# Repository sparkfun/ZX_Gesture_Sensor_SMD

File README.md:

SparkFun ZX Distance and Gesture Sensor
========================================

[*ZX Gesture Sensor (13162)*](https://www.sparkfun.com/products/13162)

The ZX Sensor works by bouncing infrared (IR) beams of light from the two LEDs on either side 
off of an object above the sensor. The bounced light returns to the receiver in the center of
the sensor, and a microcontroller on the back of the sensor interprets the data. We can read 
the results using an I2C or UART connection.

Repository Contents
-------------------

* **/Hardware** - Eagle design files (.brd, .sch)
* **/Libraries** - Arduino library and example code. For the most recent updates, make sure to check out the GitHub repo for the Arduino library linked below.
* **/Production** - Production panel files (.brd)

Documentation
--------------
* **[Library](https://github.com/sparkfun/SparkFun_ZX_Distance_and_Gesture_Sensor_Arduino_Library)** - Arduino library for the ZX Distance and Gesture Sensor.
* **[Hookup Guide](https://learn.sparkfun.com/tutorials/zx-distance-and-gesture-sensor-smd-hookup-guide)** - Basic hookup guide for the ZX Gesture Sensor.

License Information
-------------------

This product is _**open source**_! 

Please review the LICENSE.md file for license information. 

If you have any questions or concerns on licensing, please contact techsupport@sparkfun.com.

Distributed as-is; no warranty is given.

- Your friends at SparkFun.

__In Collaboration in XYZ Interactive__

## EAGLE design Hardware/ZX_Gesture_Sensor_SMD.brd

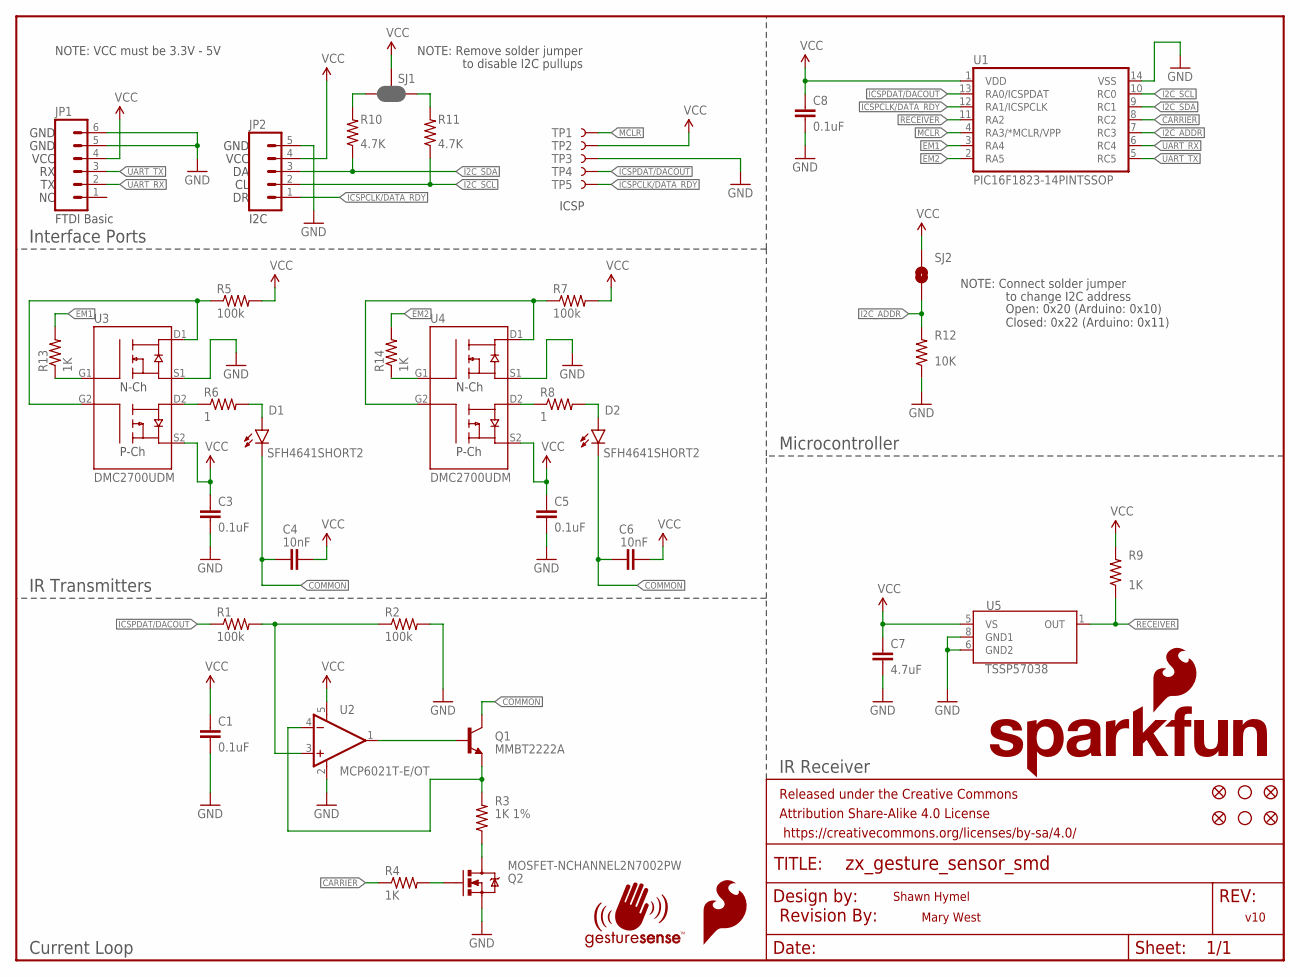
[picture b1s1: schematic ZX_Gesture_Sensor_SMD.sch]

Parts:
C1, C3, C5, C8: 0.1uF; 0603-CAP
C4, C6: 10nF; 0603-CAP
C7: 4.7uF; 0603-CAP
D1, D2: SFH4641SHORT2; SFH4641-SHORT2
FID1, FID2, FID3, FID4: FIDUCIALUFIDUCIAL; MICRO-FIDUCIAL
FRAME1: FRAME-LETTER; CREATIVE_COMMONS
JP1: M06NO_SILK_FEMALE_PTH; 1X06_NO_SILK
JP2: M05PTH; 1X05
LOGO1: REVISION
LOGO2: SFE_LOGO_FLAME.1_INCH; SFE_LOGO_FLAME_.1
Q1: MMBT2222A; SOT23-3
Q2: MOSFET-NCHANNEL2N7002PW; SOT323
R1, R2, R5, R7: 100k; 0603-RES
R3: 1K 1%; 0603-RES
R4, R9, R13, R14: 1K; 0603-RES
R6, R8: 1; 0603-RES
R10, R11: 4.7K; 0603-RES
R12: 10K; 0603-RES
SJ1: JUMPER-PAD-3-NC_BY_PASTE; PAD-JUMPER-3-NC_BY_PASTE_YES_SILK_FULL_BOX
SJ2: JUMPER-PAD-2-NOYES_SILK; PAD-JUMPER-2-NO_YES_SILK
STANDOFF1, STANDOFF2: STAND-OFF
TP1, TP2, TP3, TP4, TP5: TEST-POINT3X4; PAD.03X.04
U1: PIC16F1823-14PINTSSOP; TSSOP14
U2: MCP6021T-E/OT; SOT23-5
U3, U4: DMC2700UDM; SOT26
U5: TSSP57038; TSOP572
U$5: SFE_LOGO_NAME_FLAME.1_INCH; SFE_LOGO_NAME_FLAME_.1
U$6: GESTURESENSE_LOGOSTEXT; GESTURESENSE_TEXT

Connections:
CARRIER: R4.1, U1.8 (RC2)
COMMON: C4.1, C6.1, D1.C, D2.C, Q1.3 (C)
EM1: R13.2, U1.3 (RA4)
EM2: R14.2, U1.2 (RA5)
GND: C1.2, C3.2, C5.2, C7.2, C8.2, JP1.5, JP1.6, JP2.5, Q2.2 (S), R2.2, R12.1, TP3.P$1, U1.14 (VSS), U2.2 (V-), U3.S1, U4.S1, U5.6 (GND2), U5.8 (GND1)
I2C_ADDR: R12.2, SJ2.1, U1.7 (RC3)
I2C_SCL: JP2.2, R11.1, U1.10 (RC0)
I2C_SDA: JP2.3, R10.1, U1.9 (RC1)
ICSPCLK/DATA_RDY: JP2.1, TP5.P$1, U1.12 (RA1/ICSPCLK)
ICSPDAT/DACOUT: R1.1, TP4.P$1, U1.13 (RA0/ICSPDAT)
MCLR: TP1.P$1, U1.4 (RA3/*MCLR/VPP)
unnamed: R1.2, R2.1, U2.3 (+IN)
unnamed: Q1.2 (E), R3.2, U2.4 (-IN)
unnamed: Q1.1 (B), U2.1 (OUT)
unnamed: Q2.3 (D), R3.1
unnamed: Q2.1 (G), R4.2
unnamed: R6.1, U3.D2
unnamed: D1.A, R6.2
unnamed: R5.1, U3.D1, U3.G2
unnamed: R7.1, U4.D1, U4.G2
unnamed: R10.2, SJ1.3
unnamed: R8.1, U4.D2
unnamed: D2.A, R8.2
unnamed: R11.2, SJ1.1
unnamed: R13.1, U3.G1
unnamed: R14.1, U4.G1
RECEIVER: R9.1, U1.11 (RA2), U5.1 (OUT)
UART_RX: JP1.2, U1.6 (RC4)
UART_TX: JP1.3, U1.5 (RC5)
VCC: C1.1, C3.1, C4.2, C5.1, C6.2, C7.1, C8.1, JP1.4, JP2.4, R5.2, R7.2, R9.2, SJ1.2, SJ2.2, TP2.P$1, U1.1 (VDD), U2.5 (V+), U3.S2, U4.S2, U5.5 (VS)

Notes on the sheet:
FTDI Basic
I2C
ICSP
NOTE: Remove solder jumper
to disable I2C pullups
NOTE: Connect solder jumper
to change I2C address
Open: 0x20 (Arduino: 0x10) Closed: 0x22 (Arduino: 0x11)
Interface Ports
IR Transmitters
Current Loop
Microcontroller
IR Receiver
VCC
GND
NOTE: VCC must be 3.3V - 5V
Shawn Hymel
Mary West
v10

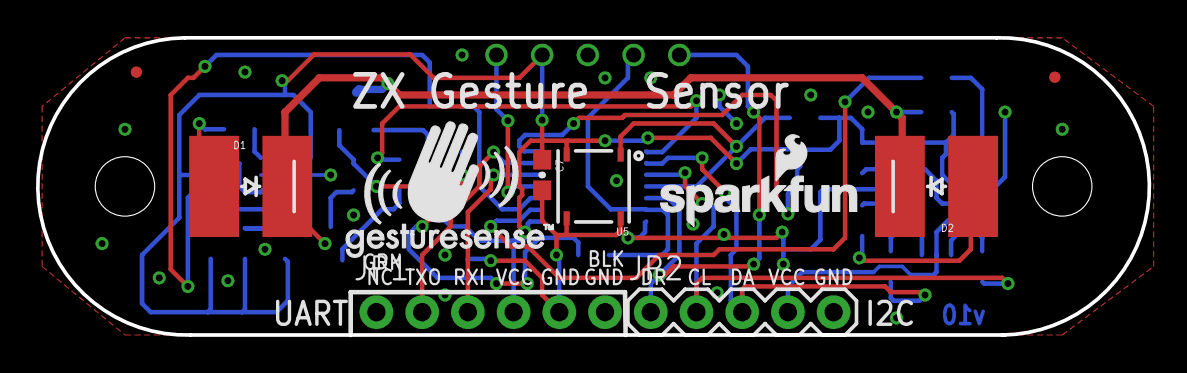
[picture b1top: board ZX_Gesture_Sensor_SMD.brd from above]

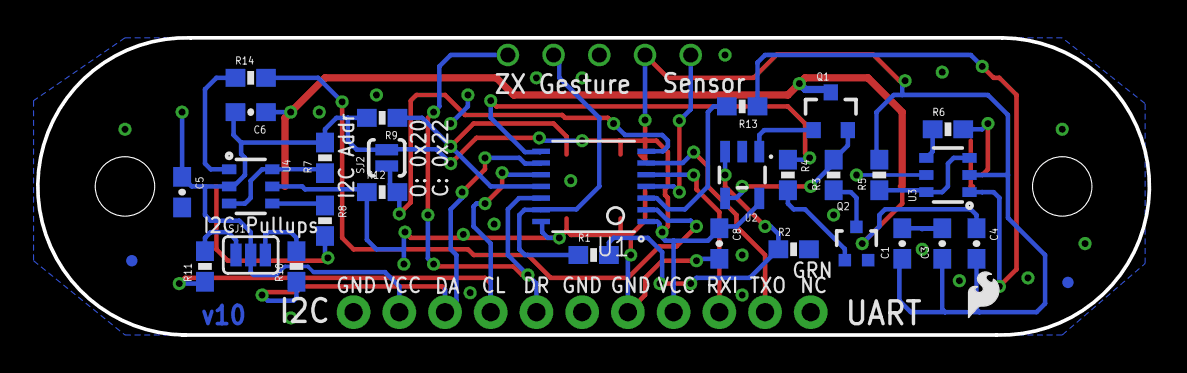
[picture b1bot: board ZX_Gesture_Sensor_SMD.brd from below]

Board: 2 copper layers, 61.8 x 16.5 mm, 50 parts (36 on the bottom side), 30 nets.

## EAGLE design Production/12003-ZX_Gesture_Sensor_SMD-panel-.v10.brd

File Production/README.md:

SparkFun <PRODUCT NAME> Production Files
=========================================

These are the production files SparkFun uses for printing PCBs.

License Information
-------------------
This product is open source! 
The hardware is released under [Creative Commons ShareAlike 4.0 International](https://creativecommons.org/licenses/by-sa/4.0/).
Please use, reuse, and modify these files as you see fit. Please maintain attribution to SparkFun Electronics and release anything derivative under the same license.

Distributed as-is; no warranty is given.

- Your friends at SparkFun.

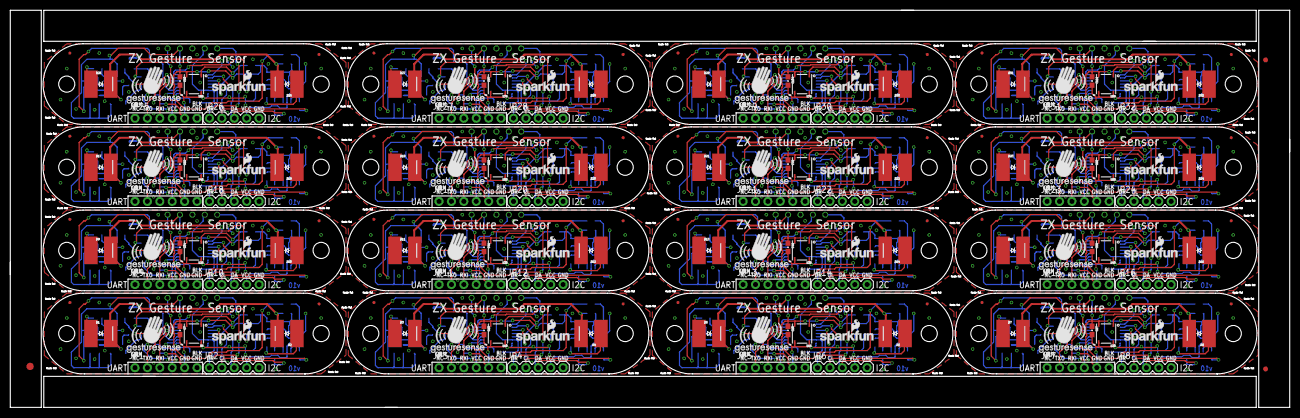
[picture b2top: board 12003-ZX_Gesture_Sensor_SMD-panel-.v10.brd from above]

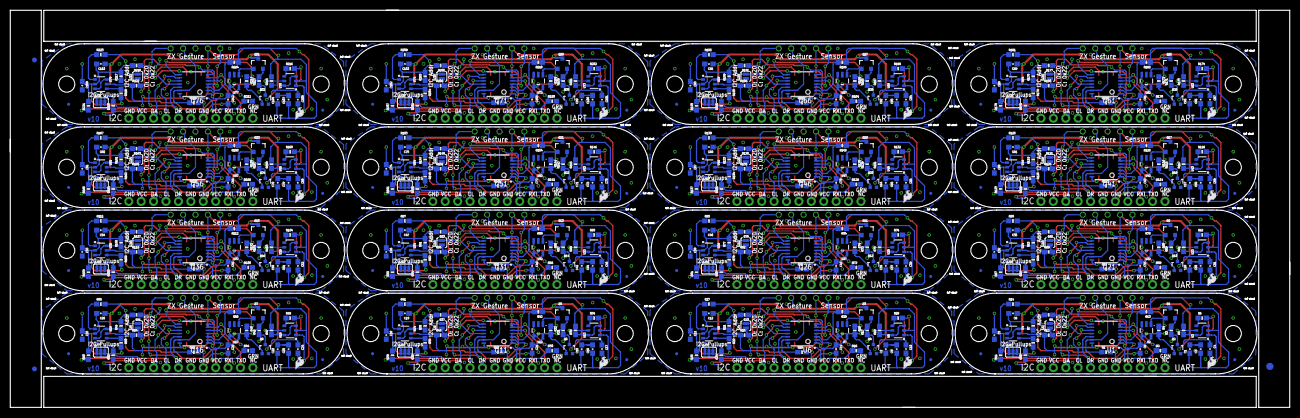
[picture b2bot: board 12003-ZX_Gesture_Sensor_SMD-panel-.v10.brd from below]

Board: 2 copper layers, 261.9 x 81.3 mm, 774 parts (579 on the bottom side), 480 nets.

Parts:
C1, C2, C3, C5, C8, C9, C11, C14, C15, C16, C18, C21, C22, C23, C25, C28, C29, C30, C32, C35, C36, C37, C39, C42, C43, C44, C46, C49, C50, C51, C53, C56, C57, C58, C60, C63, C64, C65, C67, C70, C71, C72, C74, C77, C78, C79, C81, C84, C85, C86, C88, C91, C92, C93, C95, C98, C99, C100, C102, C105, C106, C107, C109, C112: 0.1uF; 0603-CAP
C4, C6, C10, C12, C17, C19, C24, C26, C31, C33, C38, C40, C45, C47, C52, C54, C59, C61, C66, C68, C73, C75, C80, C82, C87, C89, C94, C96, C101, C103, C108, C110: 10nF; 0603-CAP
C7, C13, C20, C27, C34, C41, C48, C55, C62, C69, C76, C83, C90, C97, C104, C111: 4.7uF; 0603-CAP
D1, D2, D3, D4, D5, D6, D7, D8, D9, D10, D11, D12, D13, D14, D15, D16, D17, D18, D19, D20, D21, D22, D23, D24, D25, D26, D27, D28, D29, D30, D31, D32: SFH4641SHORT2; SFH4641-SHORT2
E$1, E$2: FIDUCIAL-1.5X3
E$3, E$4, E$7, E$8: FIDUCIAL-1X2
FID1, FID2, FID3, FID4, FID5, FID6, FID7, FID8, FID9, FID10, FID11, FID12, FID13, FID14, FID15, FID16, FID17, FID18, FID19, FID20, FID21, FID22, FID23, FID24, FID25, FID26, FID27, FID28, FID29, FID30, FID31, FID32, FID33, FID34, FID35, FID36, FID37, FID38, FID39, FID40, FID41, FID42, FID43, FID44, FID45, FID46, FID47, FID48, FID49, FID50, FID51, FID52, FID53, FID54, FID55, FID56, FID57, FID58, FID59, FID60, FID61, FID62, FID63, FID64: FIDUCIALUFIDUCIAL; MICRO-FIDUCIAL
JP1, JP3, JP5, JP7, JP9, JP11, JP13, JP15, JP17, JP19, JP21, JP23, JP25, JP27, JP29, JP31: 1X06_NO_SILK
JP2, JP4, JP6, JP8, JP10, JP12, JP14, JP16, JP18, JP20, JP22, JP24, JP26, JP28, JP30, JP32: 1X05
LOGO1, LOGO2, LOGO3, LOGO4, LOGO5, LOGO6, LOGO7, LOGO8, LOGO9, LOGO10, LOGO11, LOGO12, LOGO13, LOGO14, LOGO15, LOGO16: SFE_LOGO_FLAME.1_INCH; SFE_LOGO_FLAME_.1
Q1, Q3, Q5, Q7, Q9, Q11, Q13, Q15, Q17, Q19, Q21, Q23, Q25, Q27, Q29, Q31: MMBT2222A; SOT23-3
Q2, Q4, Q6, Q8, Q10, Q12, Q14, Q16, Q18, Q20, Q22, Q24, Q26, Q28, Q30, Q32: MOSFET-NCHANNEL2N7002PW; SOT323
R1, R2, R5, R7, R15, R16, R19, R21, R29, R30, R33, R35, R43, R44, R47, R49, R57, R58, R61, R63, R71, R72, R75, R77, R85, R86, R89, R91, R99, R100, R103, R105, R113, R114, R117, R119, R127, R128, R131, R133, R141, R142, R145, R147, R155, R156, R159, R161, R169, R170, R173, R175, R183, R184, R187, R189, R197, R198, R201, R203, R211, R212, R215, R217: 100k; 0603-RES
R3, R17, R31, R45, R59, R73, R87, R101, R115, R129, R143, R157, R171, R185, R199, R213: 1K 1%; 0603-RES
R4, R9, R13, R14, R18, R23, R27, R28, R32, R37, R41, R42, R46, R51, R55, R56, R60, R65, R69, R70, R74, R79, R83, R84, R88, R93, R97, R98, R102, R107, R111, R112, R116, R121, R125, R126, R130, R135, R139, R140, R144, R149, R153, R154, R158, R163, R167, R168, R172, R177, R181, R182, R186, R191, R195, R196, R200, R205, R209, R210, R214, R219, R223, R224: 1K; 0603-RES
R6, R8, R20, R22, R34, R36, R48, R50, R62, R64, R76, R78, R90, R92, R104, R106, R118, R120, R132, R134, R146, R148, R160, R162, R174, R176, R188, R190, R202, R204, R216, R218: 1; 0603-RES
R10, R11, R24, R25, R38, R39, R52, R53, R66, R67, R80, R81, R94, R95, R108, R109, R122, R123, R136, R137, R150, R151, R164, R165, R178, R179, R192, R193, R206, R207, R220, R221: 4.7K; 0603-RES
R12, R26, R40, R54, R68, R82, R96, R110, R124, R138, R152, R166, R180, R194, R208, R222: 10K; 0603-RES
SJ1, SJ3, SJ5, SJ7, SJ9, SJ11, SJ13, SJ15, SJ17, SJ19, SJ21, SJ23, SJ25, SJ27, SJ29, SJ31: JUMPER-PAD-3-NC_BY_PASTE; PAD-JUMPER-3-NC_BY_PASTE_YES_SILK_FULL_BOX
SJ2, SJ4, SJ6, SJ8, SJ10, SJ12, SJ14, SJ16, SJ18, SJ20, SJ22, SJ24, SJ26, SJ28, SJ30, SJ32: JUMPER-PAD-2-NOYES_SILK; PAD-JUMPER-2-NO_YES_SILK
STANDOFF1, STANDOFF2, STANDOFF3, STANDOFF4, STANDOFF5, STANDOFF6, STANDOFF7, STANDOFF8, STANDOFF9, STANDOFF10, STANDOFF11, STANDOFF12, STANDOFF13, STANDOFF14, STANDOFF15, STANDOFF16, STANDOFF17, STANDOFF18, STANDOFF19, STANDOFF20, STANDOFF21, STANDOFF22, STANDOFF23, STANDOFF24, STANDOFF25, STANDOFF26, STANDOFF27, STANDOFF28, STANDOFF29, STANDOFF30, STANDOFF31, STANDOFF32: STAND-OFF
TP1, TP2, TP3, TP4, TP5, TP6, TP7, TP8, TP9, TP10, TP11, TP12, TP13, TP14, TP15, TP16, TP17, TP18, TP19, TP20, TP21, TP22, TP23, TP24, TP25, TP26, TP27, TP28, TP29, TP30, TP31, TP32, TP33, TP34, TP35, TP36, TP37, TP38, TP39, TP40, TP41, TP42, TP43, TP44, TP45, TP46, TP47, TP48, TP49, TP50, TP51, TP52, TP53, TP54, TP55, TP56, TP57, TP58, TP59, TP60, TP61, TP62, TP63, TP64, TP65, TP66, TP67, TP68, TP69, TP70, TP71, TP72, TP73, TP74, TP75, TP76, TP77, TP78, TP79, TP80: TEST-POINT3X4; PAD.03X.04
U1, U6, U11, U16, U21, U26, U31, U36, U41, U46, U51, U56, U61, U66, U71, U76: PIC16F1823-14PINTSSOP; TSSOP14
U2, U7, U12, U17, U22, U27, U32, U37, U42, U47, U52, U57, U62, U67, U72, U77: MCP6021T-E/OT; SOT23-5
U3, U4, U8, U9, U13, U14, U18, U19, U23, U24, U28, U29, U33, U34, U38, U39, U43, U44, U48, U49, U53, U54, U58, U59, U63, U64, U68, U69, U73, U74, U78, U79: DMC2700UDM; SOT26
U5, U10, U15, U20, U25, U30, U35, U40, U45, U50, U55, U60, U65, U70, U75, U80: TSSP57038; TSOP572
U$1, U$3, U$5, U$7, U$9, U$11, U$13, U$15, U$17, U$19, U$21, U$23, U$25, U$27, U$29, U$31: SFE_LOGO_NAME_FLAME.1_INCH; SFE_LOGO_NAME_FLAME_.1
U$2, U$4, U$6, U$8, U$10, U$12, U$14, U$16, U$18, U$20, U$22, U$24, U$26, U$28, U$30, U$32: GESTURESENSE_LOGOSTEXT; GESTURESENSE_TEXT

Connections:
CARRIER: R4.1, U1.8
CARRIER1: R18.1, U6.8
CARRIER2: R32.1, U11.8
CARRIER3: R46.1, U16.8
CARRIER4: R60.1, U21.8
CARRIER5: R74.1, U26.8
CARRIER6: R88.1, U31.8
CARRIER7: R102.1, U36.8
CARRIER8: R116.1, U41.8
CARRIER9: R130.1, U46.8
CARRIER10: R144.1, U51.8
CARRIER11: R158.1, U56.8
CARRIER12: R172.1, U61.8
CARRIER13: R186.1, U66.8
CARRIER14: R200.1, U71.8
CARRIER15: R214.1, U76.8
COMMON: C4.1, C6.1, D1.C, D2.C, Q1.3
COMMON1: C10.1, C12.1, D3.C, D4.C, Q3.3
COMMON2: C17.1, C19.1, D5.C, D6.C, Q5.3
COMMON3: C24.1, C26.1, D7.C, D8.C, Q7.3
COMMON4: C31.1, C33.1, D9.C, D10.C, Q9.3
COMMON5: C38.1, C40.1, D11.C, D12.C, Q11.3
COMMON6: C45.1, C47.1, D13.C, D14.C, Q13.3
COMMON7: C52.1, C54.1, D15.C, D16.C, Q15.3
COMMON8: C59.1, C61.1, D17.C, D18.C, Q17.3
COMMON9: C66.1, C68.1, D19.C, D20.C, Q19.3
COMMON10: C73.1, C75.1, D21.C, D22.C, Q21.3
COMMON11: C80.1, C82.1, D23.C, D24.C, Q23.3
COMMON12: C87.1, C89.1, D25.C, D26.C, Q25.3
COMMON13: C94.1, C96.1, D27.C, D28.C, Q27.3
COMMON14: C101.1, C103.1, D29.C, D30.C, Q29.3
COMMON15: C108.1, C110.1, D31.C, D32.C, Q31.3
EM1: R13.2, U1.3
EM2: R14.2, U1.2
EM3: R28.2, U6.3
EM4: R27.2, U6.2
EM5: R42.2, U11.3
EM6: R41.2, U11.2
EM7: R56.2, U16.3
EM8: R55.2, U16.2
EM9: R70.2, U21.3
EM10: R69.2, U21.2
EM11: R84.2, U26.3
EM12: R83.2, U26.2
EM13: R98.2, U31.3
EM14: R97.2, U31.2
EM15: R112.2, U36.3
EM16: R111.2, U36.2
EM17: R126.2, U41.3
EM18: R125.2, U41.2
EM19: R140.2, U46.3
EM20: R139.2, U46.2
EM21: R154.2, U51.3
EM22: R153.2, U51.2
EM23: R168.2, U56.3
EM24: R167.2, U56.2
EM25: R182.2, U61.3
EM26: R181.2, U61.2
EM27: R196.2, U66.3
EM28: R195.2, U66.2
EM29: R210.2, U71.3
EM30: R209.2, U71.2
EM31: R224.2, U76.3
EM32: R223.2, U76.2
GND: C1.2, C3.2, C5.2, C7.2, C8.2, JP1.5, JP1.6, JP2.5, Q2.2, R2.2, R12.1, TP3.P$1, U1.14, U2.2, U3.S1, U4.S1, U5.6, U5.8
GND1: C2.2, C9.2, C11.2, C13.2, C14.2, JP3.5, JP3.6, JP4.5, Q4.2, R16.2, R26.1, TP7.P$1, U6.14, U7.2, U8.S1, U9.S1, U10.6, U10.8
GND2: C15.2, C16.2, C18.2, C20.2, C21.2, JP5.5, JP5.6, JP6.5, Q6.2, R30.2, R40.1, TP12.P$1, U11.14, U12.2, U13.S1, U14.S1, U15.6, U15.8
GND3: C22.2, C23.2, C25.2, C27.2, C28.2, JP7.5, JP7.6, JP8.5, Q8.2, R44.2, R54.1, TP17.P$1, U16.14, U17.2, U18.S1, U19.S1, U20.6, U20.8
GND4: C29.2, C30.2, C32.2, C34.2, C35.2, JP9.5, JP9.6, JP10.5, Q10.2, R58.2, R68.1, TP22.P$1, U21.14, U22.2, U23.S1, U24.S1, U25.6, U25.8
GND5: C36.2, C37.2, C39.2, C41.2, C42.2, JP11.5, JP11.6, JP12.5, Q12.2, R72.2, R82.1, TP27.P$1, U26.14, U27.2, U28.S1, U29.S1, U30.6, U30.8
GND6: C43.2, C44.2, C46.2, C48.2, C49.2, JP13.5, JP13.6, JP14.5, Q14.2, R86.2, R96.1, TP32.P$1, U31.14, U32.2, U33.S1, U34.S1, U35.6, U35.8
GND7: C50.2, C51.2, C53.2, C55.2, C56.2, JP15.5, JP15.6, JP16.5, Q16.2, R100.2, R110.1, TP37.P$1, U36.14, U37.2, U38.S1, U39.S1, U40.6, U40.8
GND8: C57.2, C58.2, C60.2, C62.2, C63.2, JP17.5, JP17.6, JP18.5, Q18.2, R114.2, R124.1, TP42.P$1, U41.14, U42.2, U43.S1, U44.S1, U45.6, U45.8
GND9: C64.2, C65.2, C67.2, C69.2, C70.2, JP19.5, JP19.6, JP20.5, Q20.2, R128.2, R138.1, TP47.P$1, U46.14, U47.2, U48.S1, U49.S1, U50.6, U50.8
GND10: C71.2, C72.2, C74.2, C76.2, C77.2, JP21.5, JP21.6, JP22.5, Q22.2, R142.2, R152.1, TP52.P$1, U51.14, U52.2, U53.S1, U54.S1, U55.6, U55.8
GND11: C78.2, C79.2, C81.2, C83.2, C84.2, JP23.5, JP23.6, JP24.5, Q24.2, R156.2, R166.1, TP57.P$1, U56.14, U57.2, U58.S1, U59.S1, U60.6, U60.8
GND12: C85.2, C86.2, C88.2, C90.2, C91.2, JP25.5, JP25.6, JP26.5, Q26.2, R170.2, R180.1, TP62.P$1, U61.14, U62.2, U63.S1, U64.S1, U65.6, U65.8
GND13: C92.2, C93.2, C95.2, C97.2, C98.2, JP27.5, JP27.6, JP28.5, Q28.2, R184.2, R194.1, TP67.P$1, U66.14, U67.2, U68.S1, U69.S1, U70.6, U70.8
GND14: C99.2, C100.2, C102.2, C104.2, C105.2, JP29.5, JP29.6, JP30.5, Q30.2, R198.2, R208.1, TP72.P$1, U71.14, U72.2, U73.S1, U74.S1, U75.6, U75.8
GND15: C106.2, C107.2, C109.2, C111.2, C112.2, JP31.5, JP31.6, JP32.5, Q32.2, R212.2, R222.1, TP77.P$1, U76.14, U77.2, U78.S1, U79.S1, U80.6, U80.8
I2C_ADDR: R12.2, SJ2.1, U1.7
I2C_ADDR1: R26.2, SJ4.1, U6.7
I2C_ADDR2: R40.2, SJ6.1, U11.7
I2C_ADDR3: R54.2, SJ8.1, U16.7
I2C_ADDR4: R68.2, SJ10.1, U21.7
I2C_ADDR5: R82.2, SJ12.1, U26.7
I2C_ADDR6: R96.2, SJ14.1, U31.7
I2C_ADDR7: R110.2, SJ16.1, U36.7
I2C_ADDR8: R124.2, SJ18.1, U41.7
I2C_ADDR9: R138.2, SJ20.1, U46.7
I2C_ADDR10: R152.2, SJ22.1, U51.7
I2C_ADDR11: R166.2, SJ24.1, U56.7
I2C_ADDR12: R180.2, SJ26.1, U61.7
I2C_ADDR13: R194.2, SJ28.1, U66.7
I2C_ADDR14: R208.2, SJ30.1, U71.7
I2C_ADDR15: R222.2, SJ32.1, U76.7
I2C_SCL: JP2.2, R11.1, U1.10
I2C_SCL1: JP4.2, R25.1, U6.10
I2C_SCL2: JP6.2, R39.1, U11.10
I2C_SCL3: JP8.2, R53.1, U16.10
I2C_SCL4: JP10.2, R67.1, U21.10
I2C_SCL5: JP12.2, R81.1, U26.10
I2C_SCL6: JP14.2, R95.1, U31.10
I2C_SCL7: JP16.2, R109.1, U36.10
I2C_SCL8: JP18.2, R123.1, U41.10
I2C_SCL9: JP20.2, R137.1, U46.10
I2C_SCL10: JP22.2, R151.1, U51.10
I2C_SCL11: JP24.2, R165.1, U56.10
I2C_SCL12: JP26.2, R179.1, U61.10
I2C_SCL13: JP28.2, R193.1, U66.10
I2C_SCL14: JP30.2, R207.1, U71.10
I2C_SCL15: JP32.2, R221.1, U76.10
I2C_SDA: JP2.3, R10.1, U1.9
I2C_SDA1: JP4.3, R24.1, U6.9
I2C_SDA2: JP6.3, R38.1, U11.9
I2C_SDA3: JP8.3, R52.1, U16.9
I2C_SDA4: JP10.3, R66.1, U21.9
I2C_SDA5: JP12.3, R80.1, U26.9
I2C_SDA6: JP14.3, R94.1, U31.9
I2C_SDA7: JP16.3, R108.1, U36.9
I2C_SDA8: JP18.3, R122.1, U41.9
I2C_SDA9: JP20.3, R136.1, U46.9
I2C_SDA10: JP22.3, R150.1, U51.9
I2C_SDA11: JP24.3, R164.1, U56.9
I2C_SDA12: JP26.3, R178.1, U61.9
I2C_SDA13: JP28.3, R192.1, U66.9
I2C_SDA14: JP30.3, R206.1, U71.9
I2C_SDA15: JP32.3, R220.1, U76.9
ICSPCLK/DATA_RDY: JP2.1, TP5.P$1, U1.12
ICSPCLK/DATA_RDY1: JP4.1, TP9.P$1, U6.12
ICSPCLK/DATA_RDY2: JP6.1, TP14.P$1, U11.12
ICSPCLK/DATA_RDY3: JP8.1, TP19.P$1, U16.12
ICSPCLK/DATA_RDY4: JP10.1, TP24.P$1, U21.12
ICSPCLK/DATA_RDY5: JP12.1, TP29.P$1, U26.12
ICSPCLK/DATA_RDY6: JP14.1, TP34.P$1, U31.12
ICSPCLK/DATA_RDY7: JP16.1, TP39.P$1, U36.12
ICSPCLK/DATA_RDY8: JP18.1, TP44.P$1, U41.12
ICSPCLK/DATA_RDY9: JP20.1, TP49.P$1, U46.12
ICSPCLK/DATA_RDY10: JP22.1, TP54.P$1, U51.12
ICSPCLK/DATA_RDY11: JP24.1, TP59.P$1, U56.12
ICSPCLK/DATA_RDY12: JP26.1, TP64.P$1, U61.12
ICSPCLK/DATA_RDY13: JP28.1, TP69.P$1, U66.12
ICSPCLK/DATA_RDY14: JP30.1, TP74.P$1, U71.12
ICSPCLK/DATA_RDY15: JP32.1, TP79.P$1, U76.12
ICSPDAT/DACOUT: R1.1, TP4.P$1, U1.13
ICSPDAT/DACOUT1: R15.1, TP10.P$1, U6.13
ICSPDAT/DACOUT2: R29.1, TP15.P$1, U11.13
ICSPDAT/DACOUT3: R43.1, TP20.P$1, U16.13
ICSPDAT/DACOUT4: R57.1, TP25.P$1, U21.13
ICSPDAT/DACOUT5: R71.1, TP30.P$1, U26.13
ICSPDAT/DACOUT6: R85.1, TP35.P$1, U31.13
ICSPDAT/DACOUT7: R99.1, TP40.P$1, U36.13
ICSPDAT/DACOUT8: R113.1, TP45.P$1, U41.13
ICSPDAT/DACOUT9: R127.1, TP50.P$1, U46.13
ICSPDAT/DACOUT10: R141.1, TP55.P$1, U51.13
ICSPDAT/DACOUT11: R155.1, TP60.P$1, U56.13
ICSPDAT/DACOUT12: R169.1, TP65.P$1, U61.13
ICSPDAT/DACOUT13: R183.1, TP70.P$1, U66.13
ICSPDAT/DACOUT14: R197.1, TP75.P$1, U71.13
ICSPDAT/DACOUT15: R211.1, TP80.P$1, U76.13
MCLR: TP1.P$1, U1.4
MCLR1: TP8.P$1, U6.4
MCLR2: TP13.P$1, U11.4
MCLR3: TP18.P$1, U16.4
MCLR4: TP23.P$1, U21.4
MCLR5: TP28.P$1, U26.4
MCLR6: TP33.P$1, U31.4
MCLR7: TP38.P$1, U36.4
MCLR8: TP43.P$1, U41.4
MCLR9: TP48.P$1, U46.4
MCLR10: TP53.P$1, U51.4
MCLR11: TP58.P$1, U56.4
MCLR12: TP63.P$1, U61.4
MCLR13: TP68.P$1, U66.4
MCLR14: TP73.P$1, U71.4
MCLR15: TP78.P$1, U76.4
unnamed: R1.2, R2.1, U2.3
unnamed: Q1.2, R3.2, U2.4
unnamed: Q1.1, U2.1
unnamed: Q2.3, R3.1
unnamed: Q2.1, R4.2
unnamed: R6.1, U3.D2
unnamed: D1.A, R6.2
unnamed: R5.1, U3.D1, U3.G2
unnamed: R7.1, U4.D1, U4.G2
unnamed: R10.2, SJ1.3
unnamed: R8.1, U4.D2
unnamed: D2.A, R8.2
unnamed: R11.2, SJ1.1
unnamed: R13.1, U3.G1
unnamed: R14.1, U4.G1
unnamed: R15.2, R16.1, U7.3
unnamed: Q3.1, U7.1
unnamed: Q4.3, R17.1
unnamed: Q4.1, R18.2
unnamed: Q3.2, R17.2, U7.4
unnamed: R20.1, U8.D2
unnamed: D3.A, R20.2
unnamed: R19.1, U8.D1, U8.G2
unnamed: R21.1, U9.D1, U9.G2
unnamed: R22.1, U9.D2
unnamed: R24.2, SJ3.3
unnamed: R25.2, SJ3.1
unnamed: R27.1, U9.G1
unnamed: R28.1, U8.G1
unnamed: D4.A, R22.2
unnamed: R29.2, R30.1, U12.3
unnamed: Q5.1, U12.1
unnamed: Q6.3, R31.1
unnamed: Q6.1, R32.2
unnamed: Q5.2, R31.2, U12.4
unnamed: R34.1, U13.D2
unnamed: D5.A, R34.2
unnamed: R33.1, U13.D1, U13.G2
unnamed: R35.1, U14.D1, U14.G2
unnamed: R36.1, U14.D2
unnamed: R38.2, SJ5.3
unnamed: R39.2, SJ5.1
unnamed: R41.1, U14.G1
unnamed: R42.1, U13.G1
unnamed: D6.A, R36.2
unnamed: R43.2, R44.1, U17.3
unnamed: Q7.1, U17.1
unnamed: Q8.3, R45.1
unnamed: Q8.1, R46.2
unnamed: Q7.2, R45.2, U17.4
unnamed: R48.1, U18.D2
unnamed: D7.A, R48.2
unnamed: R47.1, U18.D1, U18.G2
unnamed: R49.1, U19.D1, U19.G2
unnamed: R50.1, U19.D2
unnamed: R52.2, SJ7.3
unnamed: R53.2, SJ7.1
unnamed: R55.1, U19.G1
unnamed: R56.1, U18.G1
unnamed: D8.A, R50.2
unnamed: R57.2, R58.1, U22.3
unnamed: Q9.1, U22.1
unnamed: Q10.3, R59.1
unnamed: Q10.1, R60.2
unnamed: Q9.2, R59.2, U22.4
unnamed: R62.1, U23.D2
unnamed: D9.A, R62.2
unnamed: R61.1, U23.D1, U23.G2
unnamed: R63.1, U24.D1, U24.G2
unnamed: R64.1, U24.D2
unnamed: R66.2, SJ9.3
unnamed: R67.2, SJ9.1
unnamed: R69.1, U24.G1
unnamed: R70.1, U23.G1
unnamed: D10.A, R64.2
unnamed: R71.2, R72.1, U27.3
unnamed: Q11.1, U27.1
unnamed: Q12.3, R73.1
unnamed: Q12.1, R74.2
unnamed: Q11.2, R73.2, U27.4
unnamed: R76.1, U28.D2
unnamed: D11.A, R76.2
unnamed: R75.1, U28.D1, U28.G2
unnamed: R77.1, U29.D1, U29.G2
unnamed: R78.1, U29.D2
unnamed: R80.2, SJ11.3
unnamed: R81.2, SJ11.1
unnamed: R83.1, U29.G1
unnamed: R84.1, U28.G1
unnamed: D12.A, R78.2
unnamed: R85.2, R86.1, U32.3
unnamed: Q13.1, U32.1
unnamed: Q14.3, R87.1
unnamed: Q14.1, R88.2
unnamed: Q13.2, R87.2, U32.4
unnamed: R90.1, U33.D2
unnamed: D13.A, R90.2
unnamed: R89.1, U33.D1, U33.G2
unnamed: R91.1, U34.D1, U34.G2
unnamed: R92.1, U34.D2
unnamed: R94.2, SJ13.3
unnamed: R95.2, SJ13.1
unnamed: R97.1, U34.G1
unnamed: R98.1, U33.G1
unnamed: D14.A, R92.2
unnamed: R99.2, R100.1, U37.3
unnamed: Q15.1, U37.1
unnamed: Q16.3, R101.1
unnamed: Q16.1, R102.2
unnamed: Q15.2, R101.2, U37.4
unnamed: R104.1, U38.D2
unnamed: D15.A, R104.2
unnamed: R103.1, U38.D1, U38.G2
unnamed: R105.1, U39.D1, U39.G2
unnamed: R106.1, U39.D2
unnamed: R108.2, SJ15.3
unnamed: R109.2, SJ15.1
unnamed: R111.1, U39.G1
unnamed: R112.1, U38.G1
unnamed: D16.A, R106.2
unnamed: R113.2, R114.1, U42.3
unnamed: Q17.1, U42.1
unnamed: Q18.3, R115.1
unnamed: Q18.1, R116.2
unnamed: Q17.2, R115.2, U42.4
unnamed: R118.1, U43.D2
unnamed: D17.A, R118.2
unnamed: R117.1, U43.D1, U43.G2
unnamed: R119.1, U44.D1, U44.G2
unnamed: R120.1, U44.D2
unnamed: R122.2, SJ17.3
unnamed: R123.2, SJ17.1
unnamed: R125.1, U44.G1
unnamed: R126.1, U43.G1
unnamed: D18.A, R120.2
unnamed: R127.2, R128.1, U47.3
unnamed: Q19.1, U47.1
unnamed: Q20.3, R129.1
unnamed: Q20.1, R130.2
unnamed: Q19.2, R129.2, U47.4
unnamed: R132.1, U48.D2
unnamed: D19.A, R132.2
unnamed: R131.1, U48.D1, U48.G2
unnamed: R133.1, U49.D1, U49.G2
unnamed: R134.1, U49.D2
unnamed: R136.2, SJ19.3
unnamed: R137.2, SJ19.1
unnamed: R139.1, U49.G1
unnamed: R140.1, U48.G1
unnamed: D20.A, R134.2
unnamed: R141.2, R142.1, U52.3
unnamed: Q21.1, U52.1
unnamed: Q22.3, R143.1
unnamed: Q22.1, R144.2
unnamed: Q21.2, R143.2, U52.4
unnamed: R146.1, U53.D2
unnamed: D21.A, R146.2
unnamed: R145.1, U53.D1, U53.G2
unnamed: R147.1, U54.D1, U54.G2
unnamed: R148.1, U54.D2
unnamed: R150.2, SJ21.3
unnamed: R151.2, SJ21.1
unnamed: R153.1, U54.G1
unnamed: R154.1, U53.G1
unnamed: D22.A, R148.2
unnamed: R155.2, R156.1, U57.3
unnamed: Q23.1, U57.1
unnamed: Q24.3, R157.1
unnamed: Q24.1, R158.2
unnamed: Q23.2, R157.2, U57.4
unnamed: R160.1, U58.D2
unnamed: D23.A, R160.2
unnamed: R159.1, U58.D1, U58.G2
unnamed: R161.1, U59.D1, U59.G2
unnamed: R162.1, U59.D2
unnamed: R164.2, SJ23.3
unnamed: R165.2, SJ23.1
unnamed: R167.1, U59.G1
unnamed: R168.1, U58.G1
unnamed: D24.A, R162.2
unnamed: R169.2, R170.1, U62.3
unnamed: Q25.1, U62.1
unnamed: Q26.3, R171.1
unnamed: Q26.1, R172.2
unnamed: Q25.2, R171.2, U62.4
unnamed: R174.1, U63.D2
unnamed: D25.A, R174.2
unnamed: R173.1, U63.D1, U63.G2
unnamed: R175.1, U64.D1, U64.G2
unnamed: R176.1, U64.D2
unnamed: R178.2, SJ25.3
unnamed: R179.2, SJ25.1
unnamed: R181.1, U64.G1
unnamed: R182.1, U63.G1
unnamed: D26.A, R176.2
unnamed: R183.2, R184.1, U67.3
unnamed: Q27.1, U67.1
unnamed: Q28.3, R185.1
unnamed: Q28.1, R186.2
unnamed: Q27.2, R185.2, U67.4
unnamed: R188.1, U68.D2
unnamed: D27.A, R188.2
unnamed: R187.1, U68.D1, U68.G2
unnamed: R189.1, U69.D1, U69.G2
unnamed: R190.1, U69.D2
unnamed: R192.2, SJ27.3
unnamed: R193.2, SJ27.1
unnamed: R195.1, U69.G1
unnamed: R196.1, U68.G1
unnamed: D28.A, R190.2
unnamed: R197.2, R198.1, U72.3
unnamed: Q29.1, U72.1
unnamed: Q30.3, R199.1
unnamed: Q30.1, R200.2
unnamed: Q29.2, R199.2, U72.4
unnamed: R202.1, U73.D2
unnamed: D29.A, R202.2
unnamed: R201.1, U73.D1, U73.G2
unnamed: R203.1, U74.D1, U74.G2
unnamed: R204.1, U74.D2
unnamed: R206.2, SJ29.3
unnamed: R207.2, SJ29.1
unnamed: R209.1, U74.G1
unnamed: R210.1, U73.G1
unnamed: D30.A, R204.2
unnamed: R211.2, R212.1, U77.3
unnamed: Q31.1, U77.1
unnamed: Q32.3, R213.1
unnamed: Q32.1, R214.2
unnamed: Q31.2, R213.2, U77.4
unnamed: R216.1, U78.D2
unnamed: D31.A, R216.2
unnamed: R215.1, U78.D1, U78.G2
unnamed: R217.1, U79.D1, U79.G2
unnamed: R218.1, U79.D2
unnamed: R220.2, SJ31.3
unnamed: R221.2, SJ31.1
unnamed: R223.1, U79.G1
unnamed: R224.1, U78.G1
unnamed: D32.A, R218.2
RECEIVER: R9.1, U1.11, U5.1
RECEIVER1: R23.1, U6.11, U10.1
RECEIVER2: R37.1, U11.11, U15.1
RECEIVER3: R51.1, U16.11, U20.1
RECEIVER4: R65.1, U21.11, U25.1
RECEIVER5: R79.1, U26.11, U30.1
RECEIVER6: R93.1, U31.11, U35.1
RECEIVER7: R107.1, U36.11, U40.1
RECEIVER8: R121.1, U41.11, U45.1
RECEIVER9: R135.1, U46.11, U50.1
RECEIVER10: R149.1, U51.11, U55.1
RECEIVER11: R163.1, U56.11, U60.1
RECEIVER12: R177.1, U61.11, U65.1
RECEIVER13: R191.1, U66.11, U70.1
RECEIVER14: R205.1, U71.11, U75.1
RECEIVER15: R219.1, U76.11, U80.1
UART_RX: JP1.2, U1.6
UART_RX1: JP3.2, U6.6
UART_RX2: JP5.2, U11.6
UART_RX3: JP7.2, U16.6
UART_RX4: JP9.2, U21.6
UART_RX5: JP11.2, U26.6
UART_RX6: JP13.2, U31.6
UART_RX7: JP15.2, U36.6
UART_RX8: JP17.2, U41.6
UART_RX9: JP19.2, U46.6
UART_RX10: JP21.2, U51.6
UART_RX11: JP23.2, U56.6
UART_RX12: JP25.2, U61.6
UART_RX13: JP27.2, U66.6
UART_RX14: JP29.2, U71.6
UART_RX15: JP31.2, U76.6
UART_TX: JP1.3, U1.5
UART_TX1: JP3.3, U6.5
UART_TX2: JP5.3, U11.5
UART_TX3: JP7.3, U16.5
UART_TX4: JP9.3, U21.5
UART_TX5: JP11.3, U26.5
UART_TX6: JP13.3, U31.5
UART_TX7: JP15.3, U36.5
UART_TX8: JP17.3, U41.5
UART_TX9: JP19.3, U46.5
UART_TX10: JP21.3, U51.5
UART_TX11: JP23.3, U56.5
UART_TX12: JP25.3, U61.5
UART_TX13: JP27.3, U66.5
UART_TX14: JP29.3, U71.5
UART_TX15: JP31.3, U76.5
VCC: C1.1, C3.1, C4.2, C5.1, C6.2, C7.1, C8.1, JP1.4, JP2.4, R5.2, R7.2, R9.2, SJ1.2, SJ2.2, TP2.P$1, U1.1, U2.5, U3.S2, U4.S2, U5.5
VCC1: C2.1, C9.1, C10.2, C11.1, C12.2, C13.1, C14.1, JP3.4, JP4.4, R19.2, R21.2, R23.2, SJ3.2, SJ4.2, TP6.P$1, U6.1, U7.5, U8.S2, U9.S2, U10.5
VCC2: C15.1, C16.1, C17.2, C18.1, C19.2, C20.1, C21.1, JP5.4, JP6.4, R33.2, R35.2, R37.2, SJ5.2, SJ6.2, TP11.P$1, U11.1, U12.5, U13.S2, U14.S2, U15.5
VCC3: C22.1, C23.1, C24.2, C25.1, C26.2, C27.1, C28.1, JP7.4, JP8.4, R47.2, R49.2, R51.2, SJ7.2, SJ8.2, TP16.P$1, U16.1, U17.5, U18.S2, U19.S2, U20.5
VCC4: C29.1, C30.1, C31.2, C32.1, C33.2, C34.1, C35.1, JP9.4, JP10.4, R61.2, R63.2, R65.2, SJ9.2, SJ10.2, TP21.P$1, U21.1, U22.5, U23.S2, U24.S2, U25.5
VCC5: C36.1, C37.1, C38.2, C39.1, C40.2, C41.1, C42.1, JP11.4, JP12.4, R75.2, R77.2, R79.2, SJ11.2, SJ12.2, TP26.P$1, U26.1, U27.5, U28.S2, U29.S2, U30.5
VCC6: C43.1, C44.1, C45.2, C46.1, C47.2, C48.1, C49.1, JP13.4, JP14.4, R89.2, R91.2, R93.2, SJ13.2, SJ14.2, TP31.P$1, U31.1, U32.5, U33.S2, U34.S2, U35.5
VCC7: C50.1, C51.1, C52.2, C53.1, C54.2, C55.1, C56.1, JP15.4, JP16.4, R103.2, R105.2, R107.2, SJ15.2, SJ16.2, TP36.P$1, U36.1, U37.5, U38.S2, U39.S2, U40.5
VCC8: C57.1, C58.1, C59.2, C60.1, C61.2, C62.1, C63.1, JP17.4, JP18.4, R117.2, R119.2, R121.2, SJ17.2, SJ18.2, TP41.P$1, U41.1, U42.5, U43.S2, U44.S2, U45.5
VCC9: C64.1, C65.1, C66.2, C67.1, C68.2, C69.1, C70.1, JP19.4, JP20.4, R131.2, R133.2, R135.2, SJ19.2, SJ20.2, TP46.P$1, U46.1, U47.5, U48.S2, U49.S2, U50.5
VCC10: C71.1, C72.1, C73.2, C74.1, C75.2, C76.1, C77.1, JP21.4, JP22.4, R145.2, R147.2, R149.2, SJ21.2, SJ22.2, TP51.P$1, U51.1, U52.5, U53.S2, U54.S2, U55.5
VCC11: C78.1, C79.1, C80.2, C81.1, C82.2, C83.1, C84.1, JP23.4, JP24.4, R159.2, R161.2, R163.2, SJ23.2, SJ24.2, TP56.P$1, U56.1, U57.5, U58.S2, U59.S2, U60.5
VCC12: C85.1, C86.1, C87.2, C88.1, C89.2, C90.1, C91.1, JP25.4, JP26.4, R173.2, R175.2, R177.2, SJ25.2, SJ26.2, TP61.P$1, U61.1, U62.5, U63.S2, U64.S2, U65.5
VCC13: C92.1, C93.1, C94.2, C95.1, C96.2, C97.1, C98.1, JP27.4, JP28.4, R187.2, R189.2, R191.2, SJ27.2, SJ28.2, TP66.P$1, U66.1, U67.5, U68.S2, U69.S2, U70.5
VCC14: C99.1, C100.1, C101.2, C102.1, C103.2, C104.1, C105.1, JP29.4, JP30.4, R201.2, R203.2, R205.2, SJ29.2, SJ30.2, TP71.P$1, U71.1, U72.5, U73.S2, U74.S2, U75.5
VCC15: C106.1, C107.1, C108.2, C109.1, C110.2, C111.1, C112.1, JP31.4, JP32.4, R215.2, R217.2, R219.2, SJ31.2, SJ32.2, TP76.P$1, U76.1, U77.5, U78.S2, U79.S2, U80.5

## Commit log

2015-04-22 Updating to new hardware repo layout, modifying READMEs
2015-04-22 Fixing readme formatting
2015-04-22 More formatting cleanup
2015-04-22 Adding blank link for libraries to readme
2015-04-24 Updating Libraries readme format
2015-04-28 Updating Libraries README with subtree directions
2015-05-27 Updating licensing info, adding documentation directory
2015-05-27 Updating README to reflect documentation change
2015-06-04 Fixed a pair of typos
2015-12-07 Added Linux backup files to gitignore
2016-01-08 Update README.md
    Adding graphical datasheet link to readme
2016-02-11 Update LICENSE.md
    Updated year to be current
2016-02-23 Adding *.l#? to gitignore
    ignoring eagle library backups.
2016-02-23 Deleting accidentally renamed gitignore
    drag and drop got confused by a hidden file??
2016-02-23 Ignoring eagle library backups (*.l#1, etc)
2016-03-22 Added New SCH and BRD Files
2016-03-22 Updated Board File
2016-03-22 Updated -- Placed Vias over test points
2016-03-31 Updated Board and Schematic Files
2016-03-31 Updated Board and Schematic per QC
2016-03-31 Updated Board Files per QC
2016-03-31 Updated Sch
2016-05-03 Updated Brd File
2016-05-04 Moved Programming Pins
2016-05-09 Updated Silk to include I2C adresses
2016-05-11 Changed Sch font to vector
2016-05-27 Updated board file to v03 for protos
2016-05-31 Updated Brd and Sch Files per QC review
2016-05-31 cleaning up repo
2016-09-08 V04 changes
2016-09-14 Updated Brd File per Engineering Design Review
2016-09-14 Updated Brd/Sch files per QC Review
2017-01-31 Updated SCH & BRD Files
2017-01-31 Updated BRD and SCH files
2017-01-31 updated BRD Files
2017-02-06 Updated BRD and SCH Files per Design Review
2017-03-20 -Updated v05 to v10 -moved back silk labels -all copper is unchanged from v05.
2017-03-22 -Approved DRC Erros -- Overalapping Vias and Test Points 3/22/2017
2017-03-28 panel
2017-06-01 Updated Read ME
2018-03-30 Updating pull link
    Pull text didn't have actual link to library
2018-05-10 Delete README.md
    Nothing in this path, deleting.
2018-05-10 Squashed 'Libraries/Arduino/' content from commit f6afaee
    git-subtree-dir: Libraries/Arduino
    git-subtree-split: f6afaeef8426aa26ab8c341ea9467d33714c12cb
2018-05-10 Squashed 'Libraries/Arduino/' changes from f6afaee..694cfb5
    694cfb5 Update README.md
    git-subtree-dir: Libraries/Arduino
    git-subtree-split: 694cfb57b9462c667afe94eeebdc14f0e5bf3b9e

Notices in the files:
parts and their libraries:
SparkFun-Aesthetics: Licensing: Creative Commons ShareAlike 4.0 International - https://creativecommons.org/licenses/by-sa/4.0
SparkFun-Aesthetics: Released under the Creative Commons Attribution Share-Alike 4.0 License
SparkFun-Aesthetics: Released under the Creative Commons
